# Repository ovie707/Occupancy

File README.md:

# Occupancy Modelling using Sensor Networks
Master Thesis

A system of sensors that can be spread across a building and be analyzed, in our case we are designing it for a college library. These sensory units will be used in order to estimate the number of people in each area, and the amount of time they spend in each area. This information can then be used in order to make the library more convenient for students. 

Nodes are built around Tiva-C launchpads and communicate using Xbee Pro S2Bs. The central point consists of a Raspberry Pi and another Xbee Pro S2B

# Occupancy-test
Contains older files used during undergraduate project

#Raspberry-Pi
Contains python code used on the central Raspberry Pi
RPiOccupancy (2 versions) 1 for storing data in local sqlite database and another for storing in a remote mySQL database

Each file includes a header for more info

#Tiva-C-Launchpad
Contains C code used on the Launchpad MCU to gather data from the sensors and send it to the Rapsberry Pi.

OccupancyV1-3 uses Tivaware 2.1.2.111

Current sensors:
Panasonic Grideye, SenseAir LP-8 CO2 sensor, RHT03 temperature/humidity sensor

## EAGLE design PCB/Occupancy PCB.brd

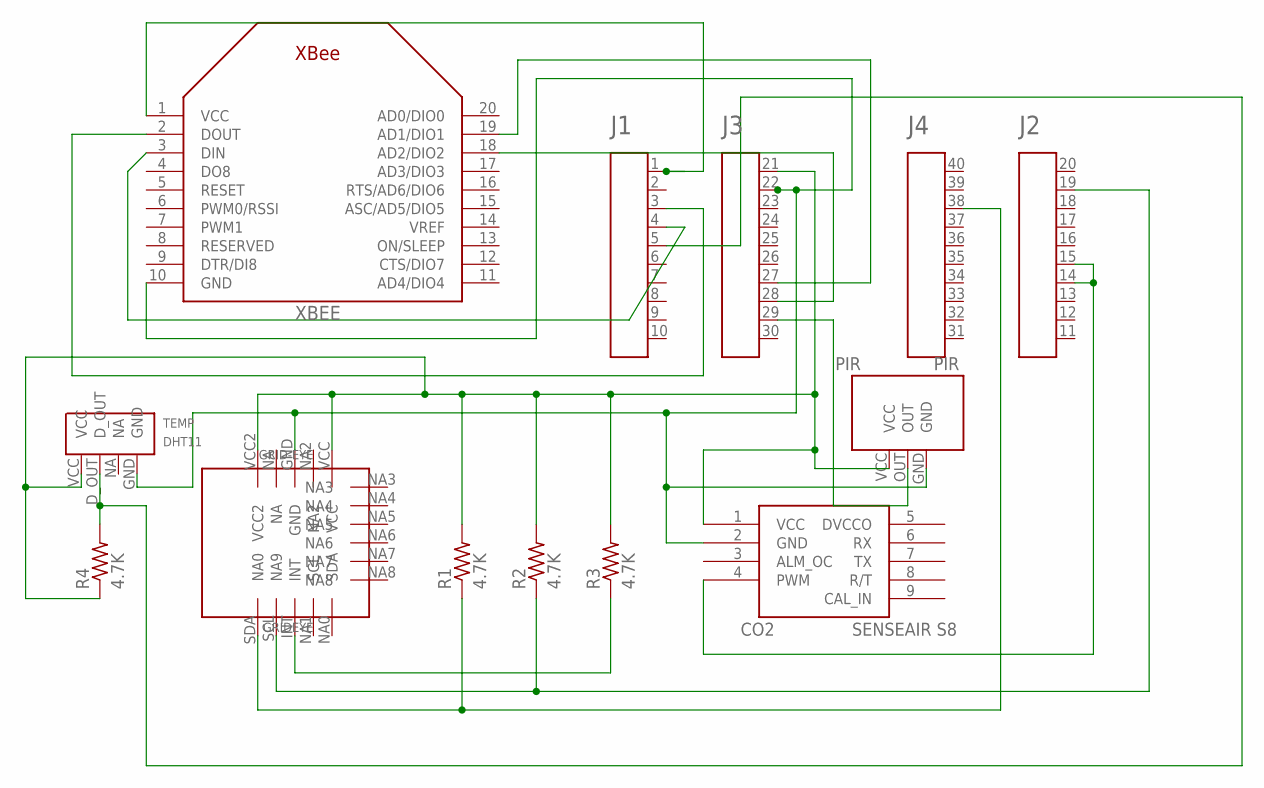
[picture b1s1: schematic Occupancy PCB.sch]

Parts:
CO2: SENSEAIR-S8-DIP
GRIDEYE: GRID-EYE-DIP
LAUNCHPAD: HEADER4X10-BOOSTERPACK; 4X10-BOOSTERPACK
PIR: PIR-DIP
R1, R2, R3, R4: 4.7K; R0805
TEMP: DHT11-DIP
XBEE: XBEE

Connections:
GND: CO2.2 (GND), GRIDEYE.GND, LAUNCHPAD.22, PIR.GND, TEMP.GND, XBEE.10 (GND)
unnamed: GRIDEYE.SDA (NA0), LAUNCHPAD.38, R1.1
unnamed: CO2.4 (PWM), LAUNCHPAD.14, LAUNCHPAD.15
unnamed: LAUNCHPAD.3, XBEE.2 (DOUT)
unnamed: LAUNCHPAD.4, XBEE.3 (DIN)
unnamed: GRIDEYE.SCL (NA9), LAUNCHPAD.19, R2.1
unnamed: GRIDEYE.INT, R3.1
unnamed: LAUNCHPAD.5, R4.2, TEMP.D_OUT
unnamed: LAUNCHPAD.27, XBEE.19 (AD1/DIO1)
unnamed: LAUNCHPAD.28, XBEE.18 (AD2/DIO2)
unnamed: LAUNCHPAD.29, PIR.OUT
VCC: CO2.1 (VCC), GRIDEYE.VCC, GRIDEYE.VCC2, LAUNCHPAD.21, PIR.VCC, R1.2, R2.2, R3.2, R4.1, TEMP.VCC
VCC3: LAUNCHPAD.1, XBEE.1 (VCC)

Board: 2 copper layers, 10 parts (5 on the bottom side), 13 nets, no tracks yet.

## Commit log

2016-02-29 Create CO2 Grid-EYE
    Code in C that runs on the Tiva Launchpad that runs the CO2 sensor and Grid-EYE.
2016-03-22 XbeeCom version 1
    Code to send small string through Xbee's using API mode
2016-03-22 Rename main.c to XbeeCom.c
2016-03-22 Current version of XbeeCom
    This code sends dummy grid eye data (128 bytes) along with a sensor unit identifier, data type and delimeter. This is the format of the packet it sends.
    17 bytes
    These bytes are used by the xBee in API mode.
    0x7E, 0x00, 0x92, 0x10, 0x01, 0x00, 0x00, 0x00, 0x00, 0x00, 0x00, 0x00, 0x00, 0xFF, 0xFE, 0x00, 0x00
    1 byte
    Sensor unit identifier. right now it's just 1, but as we add more units it will go higher
2016-03-22 Rename main.c to XbeeCom
2016-03-22 Rename XbeeCom to XbeeCom.c
2016-04-03 Update XbeeCom.c
    Updated to most recent version of this 'version'
2016-04-03 Create XbeeComms V1-3.c
    This is an updated version of XbeeComms that replaces the timer interrupt with a pin interrupt so that the launchpad can receive data requests periodically. This way the RPi can send data requests to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
2016-04-03 Update README.md
    Added descriptions for XbeeComs and XbeeComsV1-3
2016-04-08 PCB Board and Schematic Files
    Contains the .brd and .sch files as well as a .PNG file for both the board and schematic.
2016-04-08 Eagle Part Library
    This library contains the parts used for Rev B of the PCB. Parts include the DHT11, Grid-eye, Senseair S8 CO2, and PIR sensors.
2016-04-08 Added files via upload
2016-04-08 Rename LUJAN.lbr to PCB/LUJAN.lbr
2016-04-08 PCB Board and Schematic Files
2016-04-12 First integration test of sensors and xbees
    This code integrates the activation of a pin interrupt via xbee, reading of sensor data, transmitting of said data over the xbees to a central location.
2016-04-12 Rename main.c to Occupancy Test v1.1.c
2016-04-12 Delete XbeeCom.c
    Don't need this anymore due to the addition of Occupancy Testing. I still have it on Google Drive as well as local storage just in case, I just want to keep the repository organized.
2016-04-12 Delete XbeeComms V1-3.c
    Unnecessary to have since the addition of Occupancy testing. I want to keep the repository organized. I still have this file on Google drive as well as local storage.
2016-04-12 Delete Occupancy Test v1.1.c
    Moving this file to a folder to keep organized
2016-04-12 Create RPi serial format
    This specifies how to send requests to the sensor nodes from the central unit, as well as the format of the data that will be received.
2016-04-12 Update README.md
    removed section on old xbee code and added explanation of Occupancy-testing
2016-04-26 Added support for RHT03 Temp and Humidity Sensor
    The unit now reads the temperature and humidity from the RHT03. The data from the sensor is 4 bytes long and is stored in the Xbee packet between the duty cycle and the grideye data. The first two by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
2016-10-25 Update Occupancy-testingV1.2
    added variable for node identifier
2016-10-25 Create Occupancy-testingV1-2
    Creating new folder for Launchpad code
2016-10-25 Create RpiOccupancyV2
2016-10-25 Create RHT03
2016-10-25 Create CO2gridV2-3
2016-10-25 Create XbeeCommsV1-1
2016-10-25 Update README.md
    added sentence for XbeeCommsV1.1
2016-12-18 Update and rename Occupancy-testingV1-2 to OccupancyV1-3
    added PIR implementation
2017-02-03 Update to v6.1
    In the case that a node loses power or otherwise becomes unresponsive, Node discovery is performed to repopulate the list of active nodes so the program doesn't hang while trying to receive input.
2017-02-03 Stuff I've been working on recently
    NodeDiscovery discovers other nodes on the same Xbee mesh network
    RPIOccupancy-remote is the same as the other RPiOccupancy with the exception that it connects to a remote mySQL database
    sqlite animation queries a sqlite database and creates an animated heatmap of the grideye data. Can also be retrofitted to a mySQL database
2017-02-03 Rename RpiOccupancyV2 to RpiOccupancy-local
2017-02-03 Rename RpiOccupancy-local to RpiOccupancy-local.py
2017-02-03 Removed specific IP and database info
2017-02-03 Update OccupancyV1-3
2017-03-21 Occupancy V1-4 update
    02/19/2017
    only requested data from grideye when pir was triggered (should save power)
    03/03/2017
    revised PIR trigger method. A timer now counts down once the PIR is inactive. Once it reaches
    zero, the grideye isn't called for data. When the PIR is active, the timer resets.
    03/21/2017
2017-03-21 Added trigger column for grideye
    v6.1.2 (03/01/2017)
    added trigger column to database if a pixel is higher than a certain threshold
